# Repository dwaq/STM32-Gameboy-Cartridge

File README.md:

# STM32-Gameboy-Cartridge
Hardware emulation of a gameboy cartridge with a ST microcontroller

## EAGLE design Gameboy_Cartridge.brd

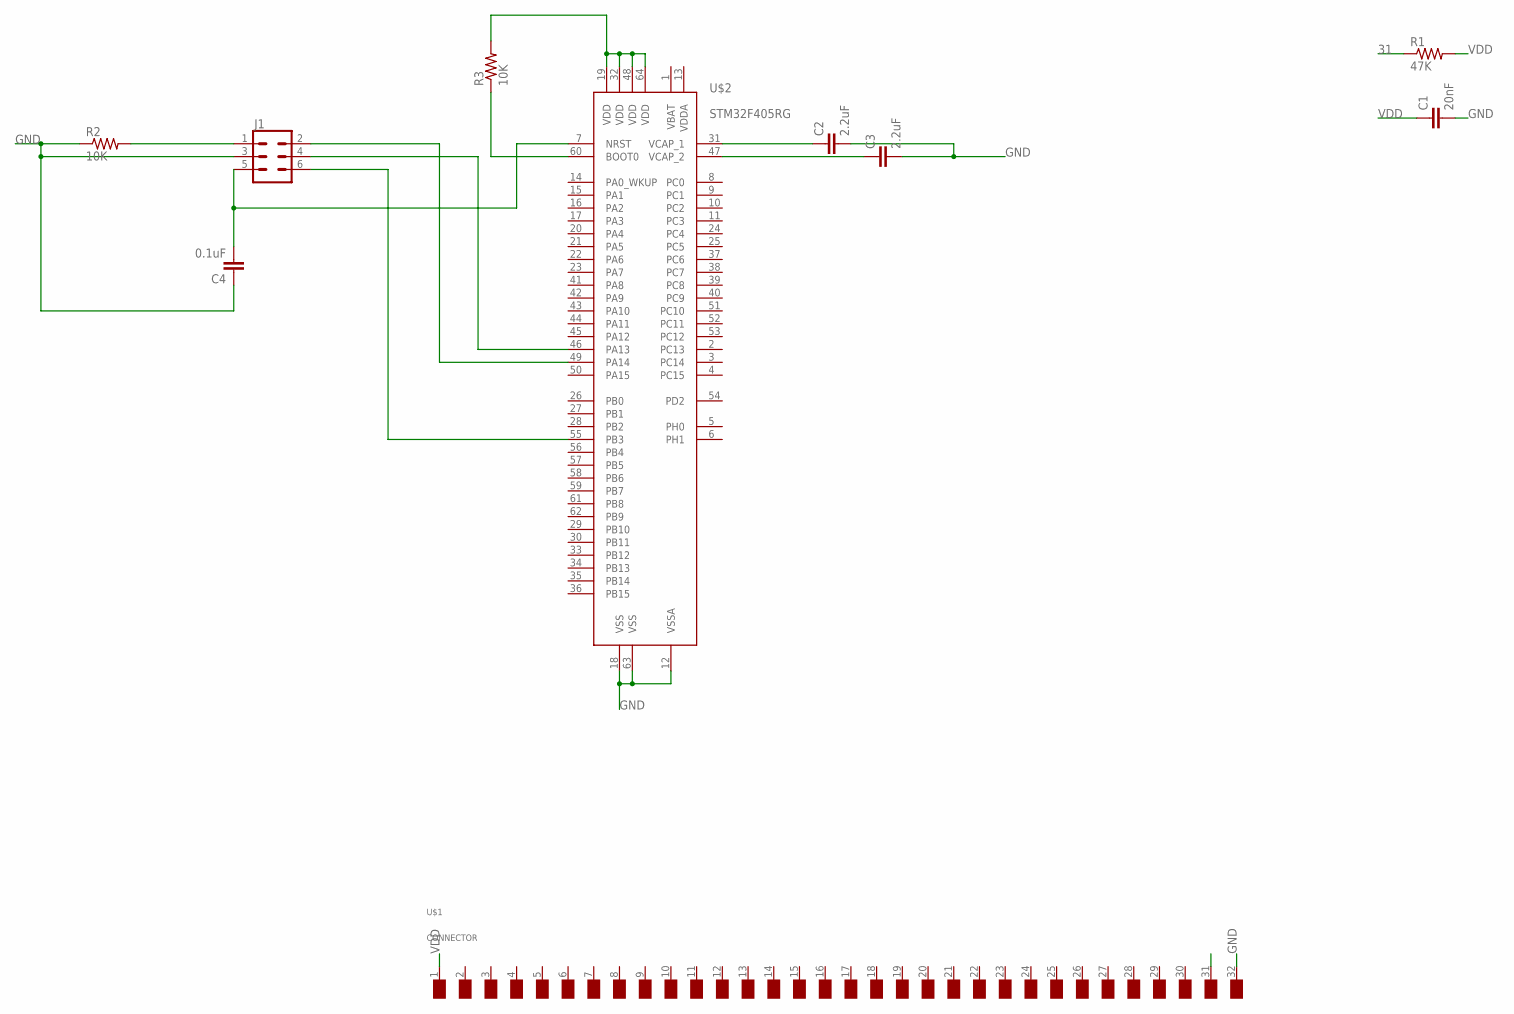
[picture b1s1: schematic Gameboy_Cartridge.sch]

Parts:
C1: 20nF; C0805
C2, C3: 2.2uF; C0805
C4: 0.1uF; C0805
J1: CONN_03X2FEMALE_SMD; 2X3_SMD
R1: 47K; M0805
R2, R3: 10K; M0805
U$1: CONNECTOR
U$2: STM32F405RG

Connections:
31: R1.1, U$1.31 (VIN)
GND: C1.2, U$1.32 (GND)
unnamed: R3.2, U$2.19 (VDD), U$2.32 (VDD), U$2.48 (VDD), U$2.64 (VDD)
unnamed: U$2.12 (VSSA), U$2.18 (VSS), U$2.63 (VSS)
unnamed: J1.1, R2.2
unnamed: C4.1, J1.3, R2.1
unnamed: J1.2, U$2.49 (PA14)
unnamed: R3.1, U$2.60 (BOOT0)
unnamed: J1.4, U$2.46 (PA13)
unnamed: C4.2, J1.5, U$2.7 (NRST)
unnamed: J1.6, U$2.55 (PB3)
unnamed: C2.1, U$2.31 (VCAP_1)
unnamed: C3.1, U$2.47 (VCAP_2)
unnamed: C2.2, C3.2
VBAT: U$2.1 (VBAT)
VDD: C1.1, R1.2, U$1.1 (VDD)
VDDA: U$2.13 (VDDA)

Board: 2 copper layers, 10 parts (0 on the bottom side), 15 nets, no tracks yet.

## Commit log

2015-12-26 add original files from Homebrew-Gameboy-Cartridge
2015-12-26 rename a couple pins on the connector
2015-12-26 remove old chips and routing
2015-12-26 new microcontroller part
2015-12-26 create package outline
2015-12-26 wrong units... use mm instead of inches
2015-12-26 rename pins
2015-12-26 aligned 1-16
2015-12-26 aligned 17-32
2015-12-26 aligned 33-48
2015-12-27 aligned 49-64
2015-12-27 add silkscreen
2015-12-27 add value and name tags
2018-01-03 ignore log files
2018-01-03 Add STM32F405RG symbol
2018-01-03 connect many pins to package
2018-01-03 connect the remaining power pins
2018-01-03 add mcu design
2018-01-03 add programming header
2018-01-03 connect mcu grounds
2018-01-03 add VCAPs
2018-01-03 can't connect VDD to 5V
2018-01-03 BOOT0 10k pullup
2018-01-03 add cap on NRST

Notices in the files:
parts and their libraries:
SparkFun-Connectors: Licensing: Creative Commons ShareAlike 4.0 International - https://creativecommons.org/licenses/by-sa/4.0
